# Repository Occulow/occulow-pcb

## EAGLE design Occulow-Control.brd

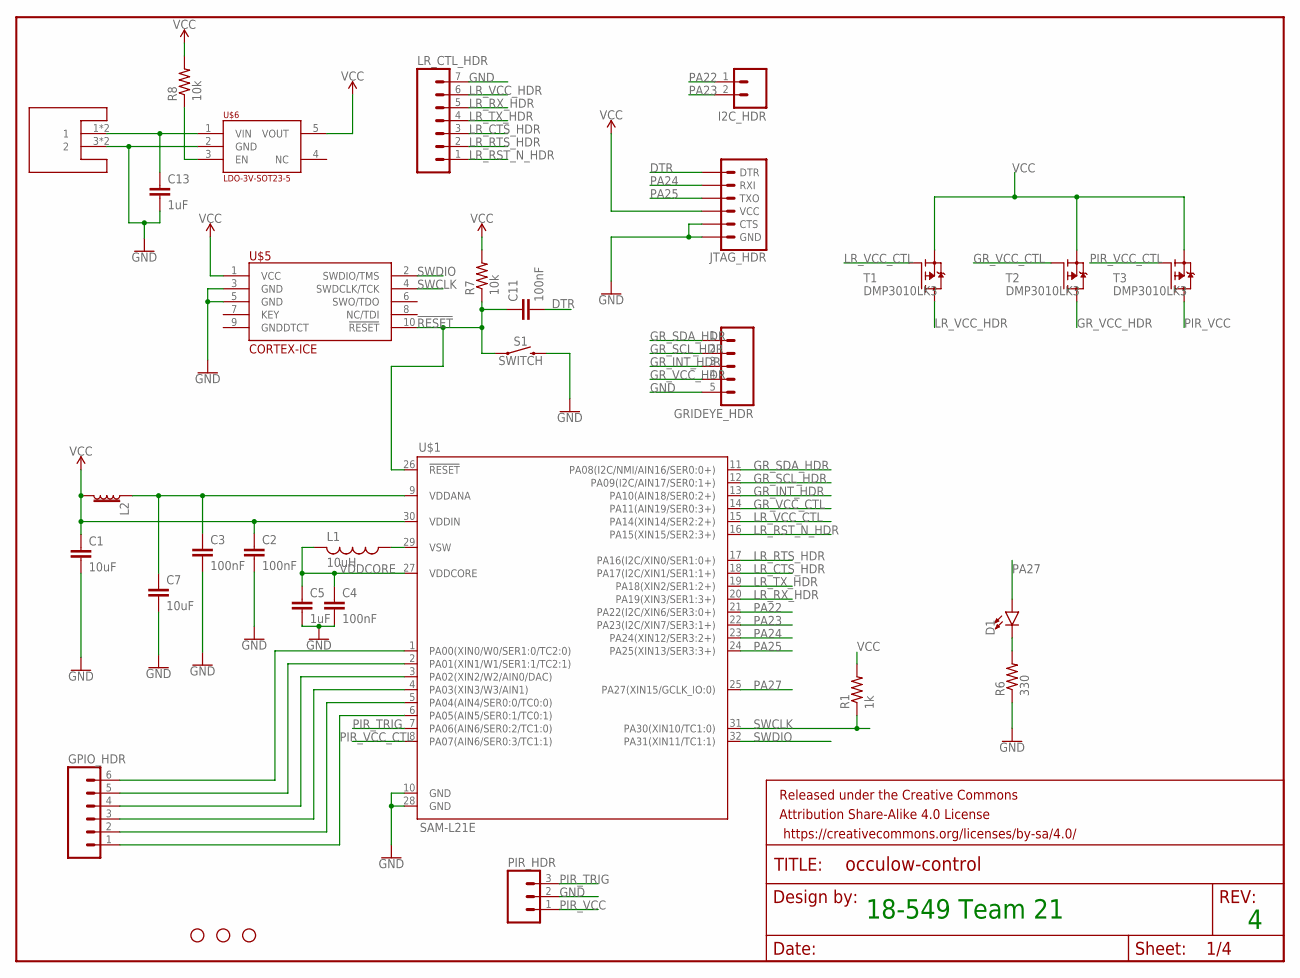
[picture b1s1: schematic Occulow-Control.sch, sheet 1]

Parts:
C1, C7: 10uF; C1206
C2, C3, C4, C11: 100nF; C1206
C5, C13: 1uF; C1206
D1: LED1206; LED-1206
FRAME1: FRAME-LETTERNO_PACKAGE; DUMMY
GPIO_HDR: M06; 06P
GRIDEYE_HDR: M05; 05P
H1, H2, H3: STAND-OFF
I2C_HDR: M02; 02P
JTAG_HDR: 6_PIN_SERIAL_TARGET; 1X06
L1: 10uH; L3225M
L2: FERRITE_BEAD-0603; 0603
LR_CTL_HDR: M07; 07P
PIR_HDR: M03; 03P
R1: 1k; R1206
R6: 330; R1206
R7, R8: 10k; R1206
S1: SWITCH; TACTILE_SWITCH_SMD_5.2MM
T1, T2, T3: DMP3010LK3; TO252
U$1: SAM-L21E; TQFP32
U$5: CORTEX-ICE; 2X5-1.27MM
U$6: LDO-3V-SOT23-5; SOT23-5L
U$7: MINI-LITE-TRAP

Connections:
!RESET: C11.1, R7.1, S1.1, S1.2 (1), U$1.26 (!RESET), U$5.10 (!RESET)
DTR: C11.2, JTAG_HDR.1 (DTR)
GND: C1.2, C2.2, C3.2, C4.2, C5.2, C7.2, C13.2, GRIDEYE_HDR.5, JTAG_HDR.5 (CTS), JTAG_HDR.6 (GND), LR_CTL_HDR.7, PIR_HDR.2, R6.1, S1.3 (2), S1.4 (2), U$1.10 (GND), U$1.28 (GND), U$5.3 (GND), U$5.5 (GND), U$6.2 (GND), U$7.3 (2), U$7.4 (2)
GR_INT_HDR: GRIDEYE_HDR.3, U$1.13 (PA10(AIN18/SER0:2+))
GR_SCL_HDR: GRIDEYE_HDR.2, U$1.12 (PA09(I2C/AIN17/SER0:1+))
GR_SDA_HDR: GRIDEYE_HDR.1, U$1.11 (PA08(I2C/NMI/AIN16/SER0:0+))
GR_VCC_CTL: T2.1 (G), U$1.14 (PA11(AIN19/SER0:3+))
GR_VCC_HDR: GRIDEYE_HDR.4, T2.3 (D)
LR_CTS_HDR: LR_CTL_HDR.3, U$1.18 (PA17(I2C/XIN1/SER1:1+))
LR_RST_N_HDR: LR_CTL_HDR.1, U$1.16 (PA15(XIN15/SER2:3+))
LR_RTS_HDR: LR_CTL_HDR.2, U$1.17 (PA16(I2C/XIN0/SER1:0+))
LR_RX_HDR: LR_CTL_HDR.5, U$1.20 (PA19(XIN3/SER1:3+))
LR_TX_HDR: LR_CTL_HDR.4, U$1.19 (PA18(XIN2/SER1:2+))
LR_VCC_CTL: T1.1 (G), U$1.15 (PA14(XIN14/SER2:2+))
LR_VCC_HDR: LR_CTL_HDR.6, T1.3 (D)
unnamed: D1.C, R6.2
unnamed: C13.1, U$6.1 (VIN), U$7.1, U$7.2 (1)
unnamed: R8.1, U$6.3 (EN)
PA00: GPIO_HDR.6, U$1.1 (PA00(XIN0/W0/SER1:0/TC2:0))
PA01: GPIO_HDR.5, U$1.2 (PA01(XIN1/W1/SER1:1/TC2:1))
PA02: GPIO_HDR.4, U$1.3 (PA02(XIN2/W2/AIN0/DAC))
PA03: GPIO_HDR.3, U$1.4 (PA03(XIN3/W3/AIN1))
PA04: GPIO_HDR.2, U$1.5 (PA04(AIN4/SER0:0/TC0:0))
PA05: GPIO_HDR.1, U$1.6 (PA05(AIN5/SER0:1/TC0:1))
PA22: I2C_HDR.1, U$1.21 (PA22(I2C/XIN6/SER3:0+))
PA23: I2C_HDR.2, U$1.22 (PA23(I2C/XIN7/SER3:1+))
PA24: JTAG_HDR.2 (RXI), U$1.23 (PA24(XIN12/SER3:2+))
PA25: JTAG_HDR.3 (TXO), U$1.24 (PA25(XIN13/SER3:3+))
PA27: D1.A, U$1.25 (PA27(XIN15/GCLK_IO:0))
PIR_TRIG: PIR_HDR.3, U$1.7 (PA06(AIN6/SER0:2/TC1:0))
PIR_VCC: PIR_HDR.1, T3.3 (D)
PIR_VCC_CTL: T3.1 (G), U$1.8 (PA07(AIN6/SER0:3/TC1:1))
SWCLK: R1.1, U$1.31 (PA30(XIN10/TC1:0)), U$5.4 (SWDCLK/TCK)
SWDIO: U$1.32 (PA31(XIN11/TC1:1)), U$5.2 (SWDIO/TMS)
VCC: C1.1, C2.1, JTAG_HDR.4 (VCC), L2.2, R1.2, R7.2, R8.2, T1.2 (S), T2.2 (S), T3.2 (S), U$1.30 (VDDIN), U$5.1 (VCC), U$6.5 (VOUT)
VDDANA: C3.1, C7.1, L2.1, U$1.9 (VDDANA)
VDDCORE: C4.1, C5.1, L1.2, U$1.27 (VDDCORE)
VSW: L1.1, U$1.29 (VSW)

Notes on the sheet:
18-549 Team 21

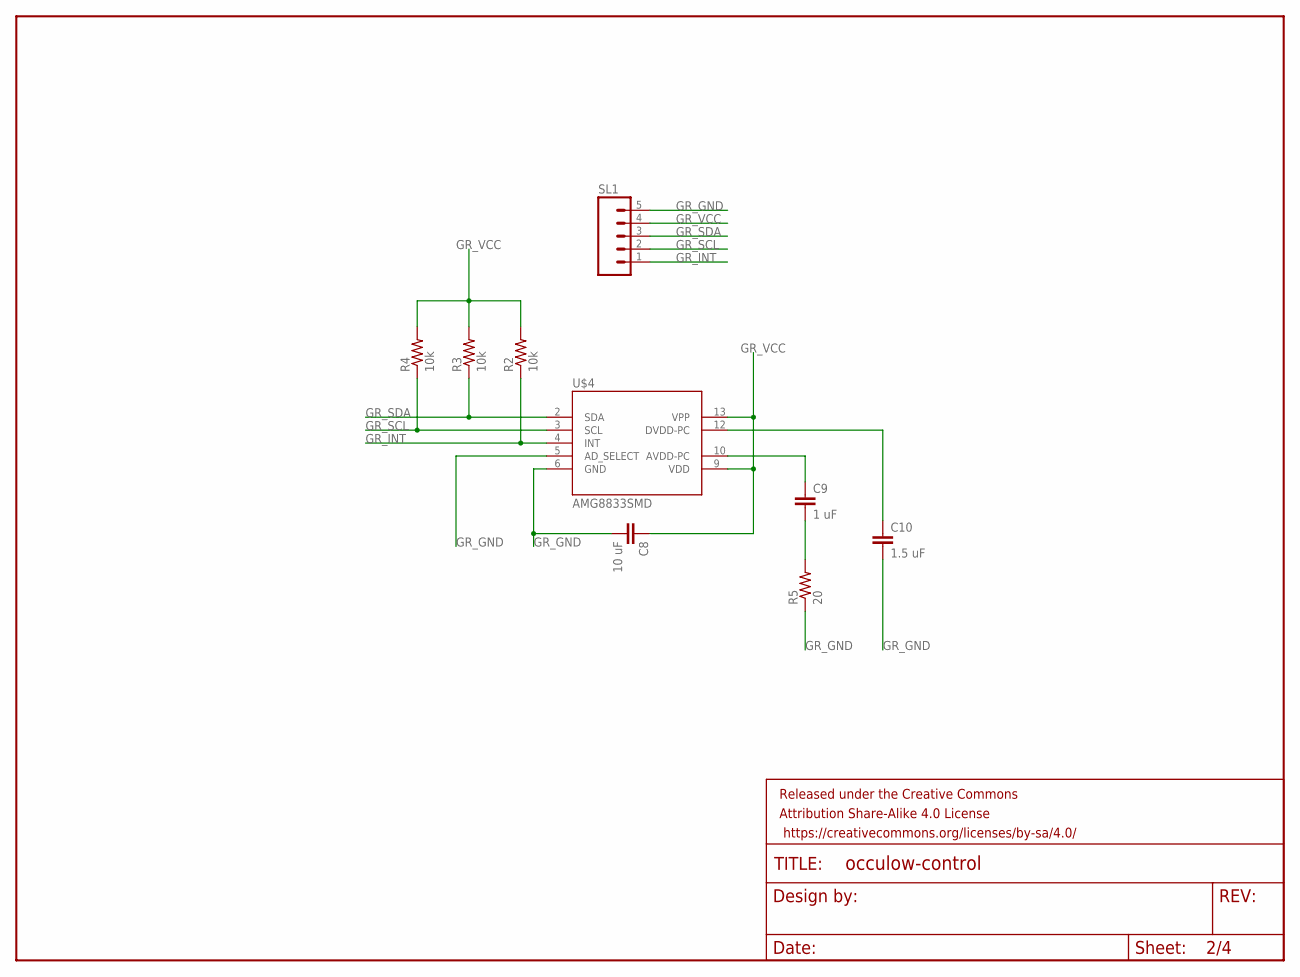
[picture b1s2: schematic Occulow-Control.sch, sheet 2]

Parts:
C8: 10 uF; C1206
C9: 1 uF; C1206
C10: 1.5 uF; C1206
FRAME2: FRAME-LETTERNO_PACKAGE; DUMMY
R2, R3, R4: 10k; R1206
R5: 20; R1206
SL1: M05; 05P
U$4: AMG8833SMD; AMG8833

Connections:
GR_GND: C8.2, C10.2, R5.1, SL1.5, U$4.5 (AD_SELECT), U$4.6 (GND)
GR_INT: R2.1, SL1.1, U$4.4 (INT)
GR_SCL: R4.1, SL1.2, U$4.3 (SCL)
GR_SDA: R3.1, SL1.3, U$4.2 (SDA)
GR_VCC: C8.1, R2.2, R3.2, R4.2, SL1.4, U$4.9 (VDD), U$4.13 (VPP)
unnamed: C9.1, U$4.10 (AVDD-PC)
unnamed: C9.2, R5.2
unnamed: C10.1, U$4.12 (DVDD-PC)

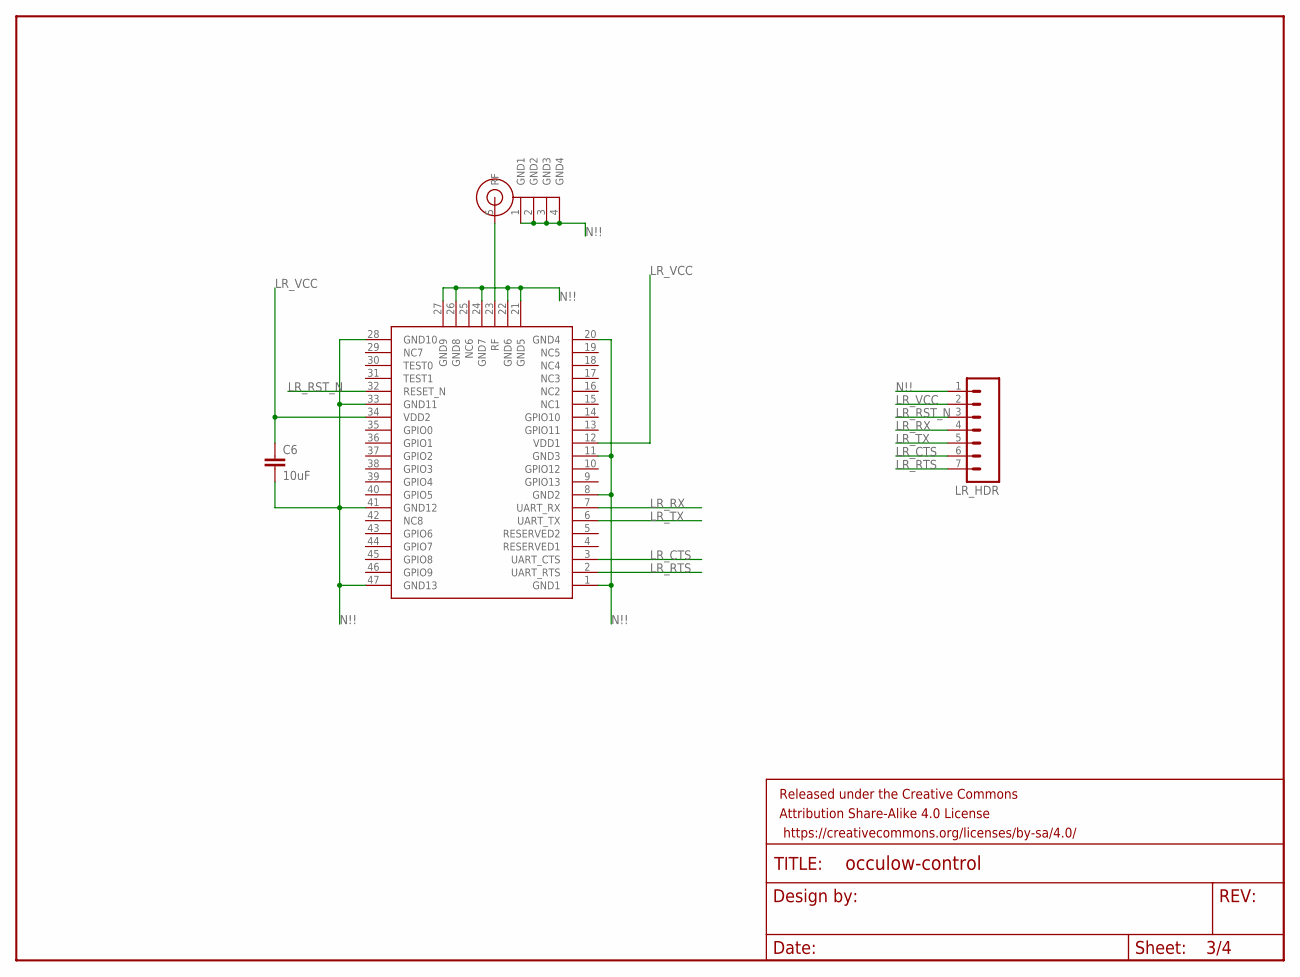
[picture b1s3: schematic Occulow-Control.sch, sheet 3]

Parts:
C6: 10uF; C1206
FRAME3: FRAME-LETTERNO_PACKAGE; DUMMY
LR_HDR: M07; 07P
U$2: RN2903
U$3: SMA-JACKFEMALE; SMA-JACK

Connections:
LR_CTS: LR_HDR.6, U$2.3 (UART_CTS)
LR_RST_N: LR_HDR.3, U$2.32 (RESET_N)
LR_RTS: LR_HDR.7, U$2.2 (UART_RTS)
LR_RX: LR_HDR.4, U$2.7 (UART_RX)
LR_TX: LR_HDR.5, U$2.6 (UART_TX)
LR_VCC: C6.1, LR_HDR.2, U$2.12 (VDD1), U$2.34 (VDD2)
N!!: C6.2, LR_HDR.1, U$2.1 (GND1), U$2.8 (GND2), U$2.11 (GND3), U$2.20 (GND4), U$2.21 (GND5), U$2.22 (GND6), U$2.24 (GND7), U$2.26 (GND8), U$2.27 (GND9), U$2.28 (GND10), U$2.33 (GND11), U$2.41 (GND12), U$2.47 (GND13), U$3.1 (GND1), U$3.2 (GND2), U$3.3 (GND3), U$3.4 (GND4)
RF: U$2.23 (RF), U$3.5 (RF)

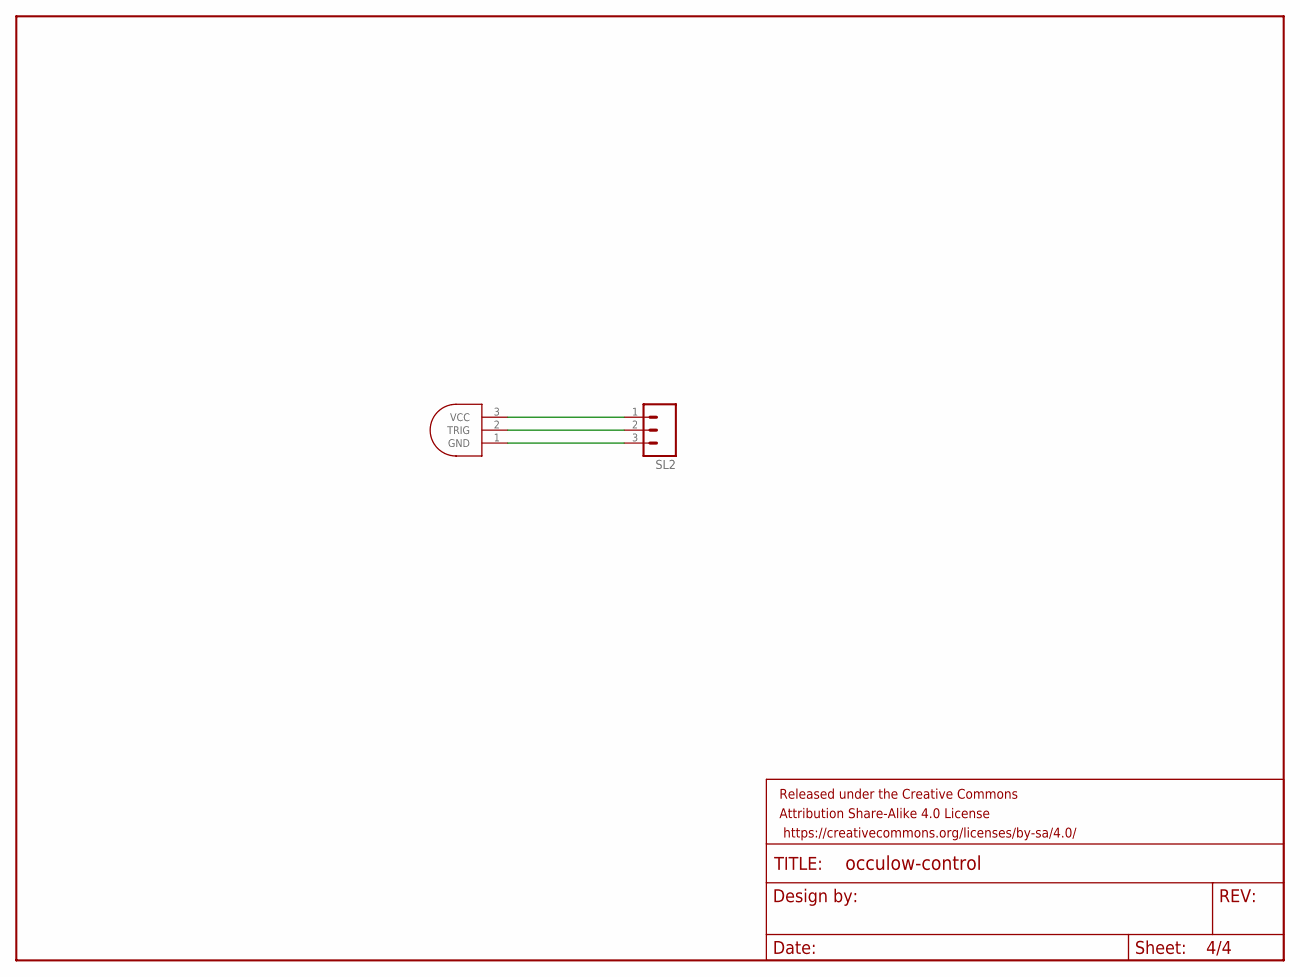
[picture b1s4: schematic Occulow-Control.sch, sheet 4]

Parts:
FRAME4: FRAME-LETTERNO_PACKAGE; DUMMY
SL2: M03; 03P
U$8: PANASONIC-PIR-DIG; TO-5

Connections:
unnamed: SL2.1, U$8.3 (VCC)
unnamed: SL2.2, U$8.2 (TRIG)
unnamed: SL2.3, U$8.1 (GND)

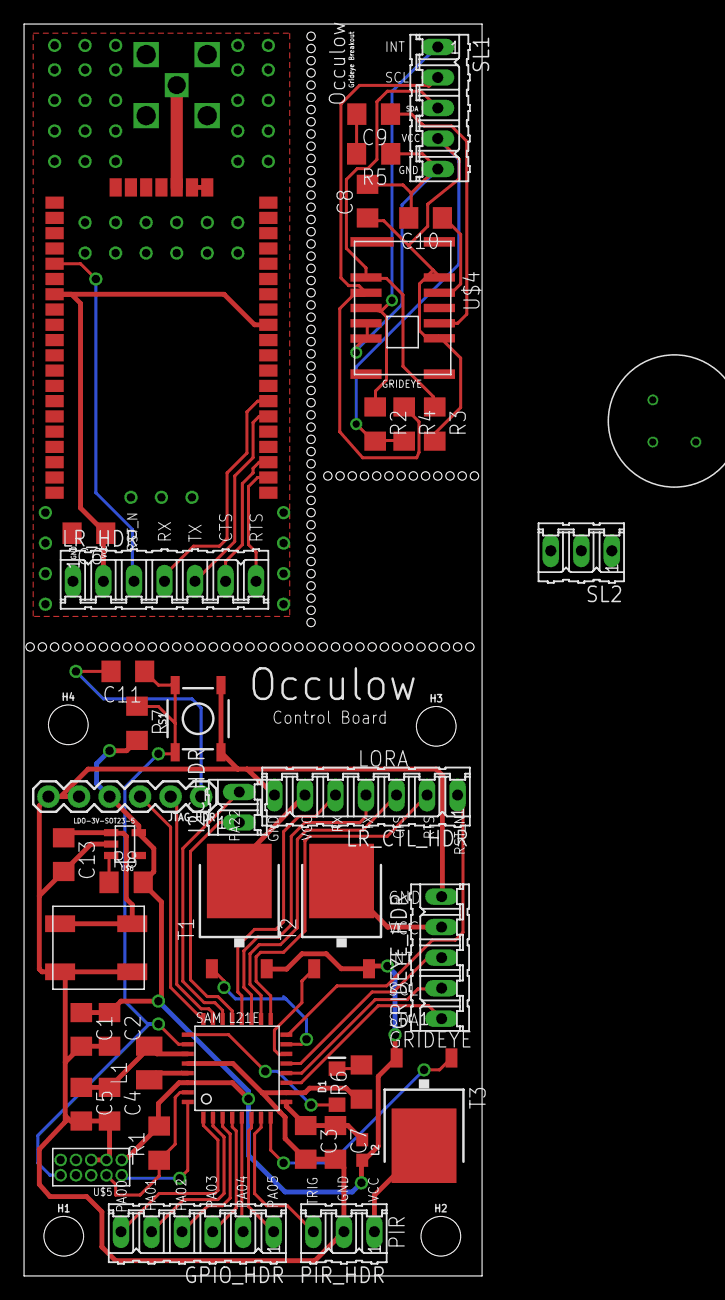
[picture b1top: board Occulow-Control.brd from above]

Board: 2 copper layers, 38.1 x 104.1 mm, 52 parts (0 on the bottom side), 57 nets.

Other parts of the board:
H4: STAND-OFF

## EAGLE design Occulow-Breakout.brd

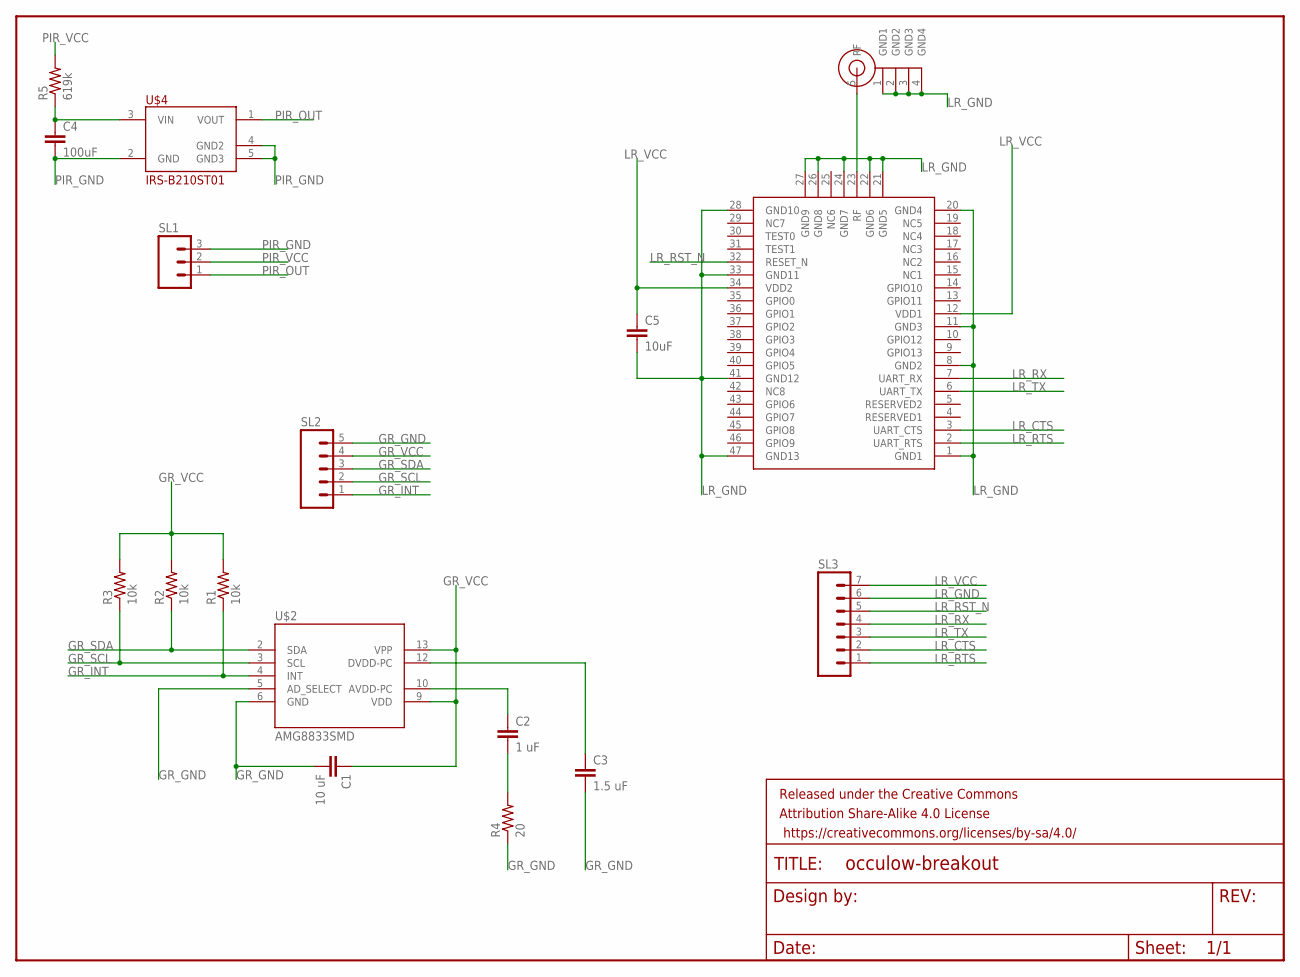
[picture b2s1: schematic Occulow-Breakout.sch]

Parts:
C1: 10 uF; C1206
C2: 1 uF; C1206
C3: 1.5 uF; C1206
C4: 100uF; C1206
C5: 10uF; C1206
FRAME1: FRAME-LETTER; CREATIVE_COMMONS
R1, R2, R3: 10k; R1206
R4: 20; R1206
R5: 619k; R1206
SL1: M03; 03P
SL2: M05; 05P
SL3: M07; 07P
U$1: RN2903
U$2: AMG8833SMD; AMG8833
U$3: SMA-JACKFEMALE; SMA-JACK
U$4: IRS-B210ST01

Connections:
GR_GND: C1.2, C3.2, R4.1, SL2.5, U$2.5 (AD_SELECT), U$2.6 (GND)
GR_INT: R1.1, SL2.1, U$2.4 (INT)
GR_SCL: R3.1, SL2.2, U$2.3 (SCL)
GR_SDA: R2.1, SL2.3, U$2.2 (SDA)
GR_VCC: C1.1, R1.2, R2.2, R3.2, SL2.4, U$2.9 (VDD), U$2.13 (VPP)
LR_CTS: SL3.2, U$1.3 (UART_CTS)
LR_GND: C5.2, SL3.6, U$1.1 (GND1), U$1.8 (GND2), U$1.11 (GND3), U$1.20 (GND4), U$1.21 (GND5), U$1.22 (GND6), U$1.24 (GND7), U$1.26 (GND8), U$1.27 (GND9), U$1.28 (GND10), U$1.33 (GND11), U$1.41 (GND12), U$1.47 (GND13), U$3.1 (GND1), U$3.2 (GND2), U$3.3 (GND3), U$3.4 (GND4)
LR_RST_N: SL3.5, U$1.32 (RESET_N)
LR_RTS: SL3.1, U$1.2 (UART_RTS)
LR_RX: SL3.4, U$1.7 (UART_RX)
LR_TX: SL3.3, U$1.6 (UART_TX)
LR_VCC: C5.1, SL3.7, U$1.12 (VDD1), U$1.34 (VDD2)
unnamed: C2.1, U$2.10 (AVDD-PC)
unnamed: C2.2, R4.2
unnamed: C3.1, U$2.12 (DVDD-PC)
unnamed: C4.1, R5.1, U$4.3 (VIN)
PIR_GND: C4.2, SL1.3, U$4.2 (GND), U$4.4 (GND2), U$4.5 (GND3)
PIR_OUT: SL1.1, U$4.1 (VOUT)
PIR_VCC: R5.2, SL1.2
RF: U$1.23 (RF), U$3.5 (RF)

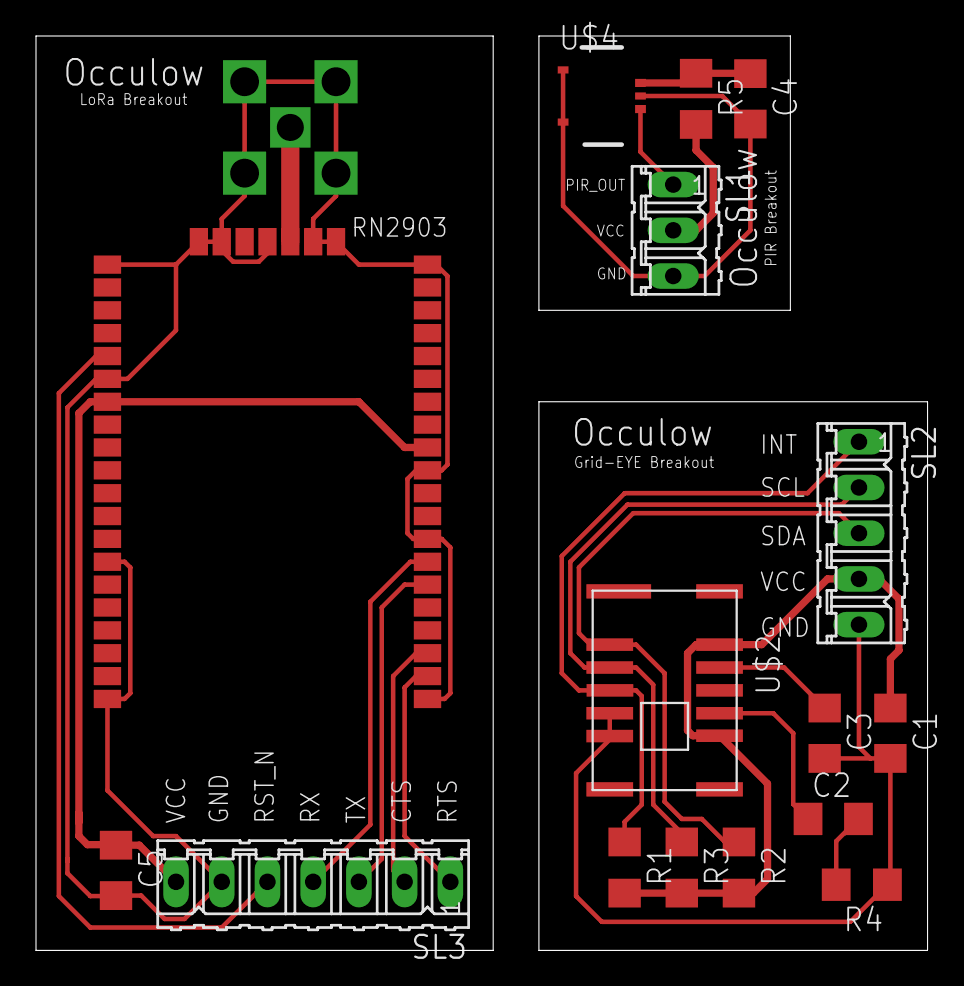
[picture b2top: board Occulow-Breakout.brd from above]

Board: 2 copper layers, 49.5 x 50.8 mm, 18 parts (0 on the bottom side), 20 nets.

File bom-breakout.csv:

Board Description:,"Breakout boards for PIR, grideye, and LoRa modules",,,,,
Team number:,21,,,,,
18-549 Bill of Materials,,,,,,
Part IDs,Manufacturer ID,Quantity,Cost,Vendor,Purchasing Link,Notes
"R1,R2,R3",311-10KERCT-ND,6,$0.10 ,Digikey,http://www.digikey.com/product-detail/en/yageo/RC1206JR-0710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,10k resistor
R4,311-20ERCT-ND,2,$0.10 ,Digikey,http://www.digikey.com/product-detail/en/yageo/RC1206JR-0720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,20 ohm resistor
R5,311-619KFRCT-ND,2,$0.10 ,Digikey,http://www.digikey.com/product-detail/en/yageo/RC1206FR-0761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,619k resistor
"C1,C5",12066D106KAT2A,4,$0.23 ,Mouser,http://www.mouser.com/ProductDetail/AVX/12066D106KAT2A/?qs=s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,10uF capacitor
C2,1206YD155KAT2A,2,$0.28 ,Mouser,http://www.mouser.com/ProductDetail/AVX/12065G105ZAT2A/?qs=s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,1uF capacitor
C3,12065G105ZAT2A,2,$1.12 ,Mouser,http://www.mouser.com/ProductDetail/AVX/1206YD155KAT2A/?qs=s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,1.5uF capacitor
C4,12066D107MAT2A,2,$0.57 ,Mouser,http://www.mouser.com/ProductDetail/AVX/12066D107MAT2A/?qs=s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,100uF capacitor
"SL1,SL2,SL3",PRT-00116,1,$1.50 ,Sparkfun,https://www.sparkfun.com/products/116,Breakaway headers

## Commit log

2017-02-25 Custom libraries, schematic for grideye
2017-02-25 Added SMA jack, RF connection for LoRa
2017-02-26 Added PIR sensor
2017-02-26 PIR power circuit
2017-02-27 Separate vcc's, headers for all
2017-02-28 Removed excessive caps, first pass at layout on 2x2
2017-02-28 Ground pins on headers
2017-02-28 Routing for lora chip
2017-02-28 Routing for grideye
2017-02-28 IR sensor layout
2017-02-28 Re-named ground for each module
2017-02-28 Panelized layout
2017-02-28 Gerber files
2017-02-28 Labels for PIR header, rearranged
2017-02-28 lora breakout labels
2017-02-28 Rearrangements and labeling
2017-02-28 Re-generate gerbers
2017-03-01 Rename caps, bom
2017-03-01 Correct reset for lora
2017-03-02 Added tplace layer for grideye
2017-03-02 Update gerbers
2017-03-02 Re-route reset, no vias
2017-03-20 Created l21 library
2017-03-22 Updated sam lbr to ease schematic dev
2017-03-23 Start of power circuit for sam chip
2017-03-23 Port lora module
2017-03-24 Lora and SAM chip integrated
2017-03-24 Split boms, started bom for control
2017-03-24 Moved lora off i2c pins, grideye header
2017-03-25 PIR control header, unused gpio to header
2017-03-25 Moved header pins around, serial debugger header, JST connector
2017-03-25 Inductor on VSW for switching power mode
2017-03-26 Fixed power filtering circuit
2017-03-26 Ferrite bead, changed inductor package
2017-03-27 Modified assignments to ease layout
2017-03-27 Standoffs
2017-03-27 First pass at board
2017-03-27 routed unused header
2017-03-27 Grideye, PIR, most power routing
2017-03-27 First pass at full routing
2017-03-27 Moved center
2017-03-27 Added vias for RF
2017-03-28 Changed to breakouts, added sheets
2017-03-28 SAM portion fully routed
2017-03-28 Lora routed
2017-03-28 All routed
2017-03-28 Added holes for panelization
2017-03-28 Added vias on lora breakout
2017-03-28 Attempted to slim down grideye board
2017-03-28 Moved grideye to the top, added more perforation holes
2017-03-29 Ground plane
2017-03-30 Labels for most headers, moved some ground vias
2017-03-30 Nice titles
2017-03-31 Control gerber files
2017-04-10 Move schematic grideye pins to i2c pads, fixes #2
2017-04-10 Updated debug header, re-routed grideye header
2017-04-10 No VDDCORE power, all vcc. Fixes #9
2017-04-10 Added LED status, bom. Fixes #6"
2017-04-11 Added vcc pull up for reset and button switch. Fixes #7
2017-04-11 Replaced extra header with JTAG and i2c headers. Fixes #4
2017-04-12 Created 2 wire trap lib, placed in schematic
2017-04-12 Added lib for ldo voltage regulator, placed in schematic. No layout
2017-04-12 Added pull-up for ldo enable
2017-04-12 Routed voltage regulator and new power connector
2017-04-12 Update bom
2017-04-12 Added pir lib, schem. No layout
2017-04-12 Added 549 cam file
2017-04-12 Generate gerber files
2017-04-24 Create LICENSE
2021-01-13 Rename 18549-gerb274x.cam to Roberta Jacobo

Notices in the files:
parts and their libraries:
SparkFun-Aesthetics: Licensing: Creative Commons ShareAlike 4.0 International - https://creativecommons.org/licenses/by-sa/4.0
SparkFun-Aesthetics: Released under the Creative Commons Attribution Share-Alike 4.0 License
SparkFun-Aesthetics: https://creativecommons.org/licenses/by-sa/4.0
